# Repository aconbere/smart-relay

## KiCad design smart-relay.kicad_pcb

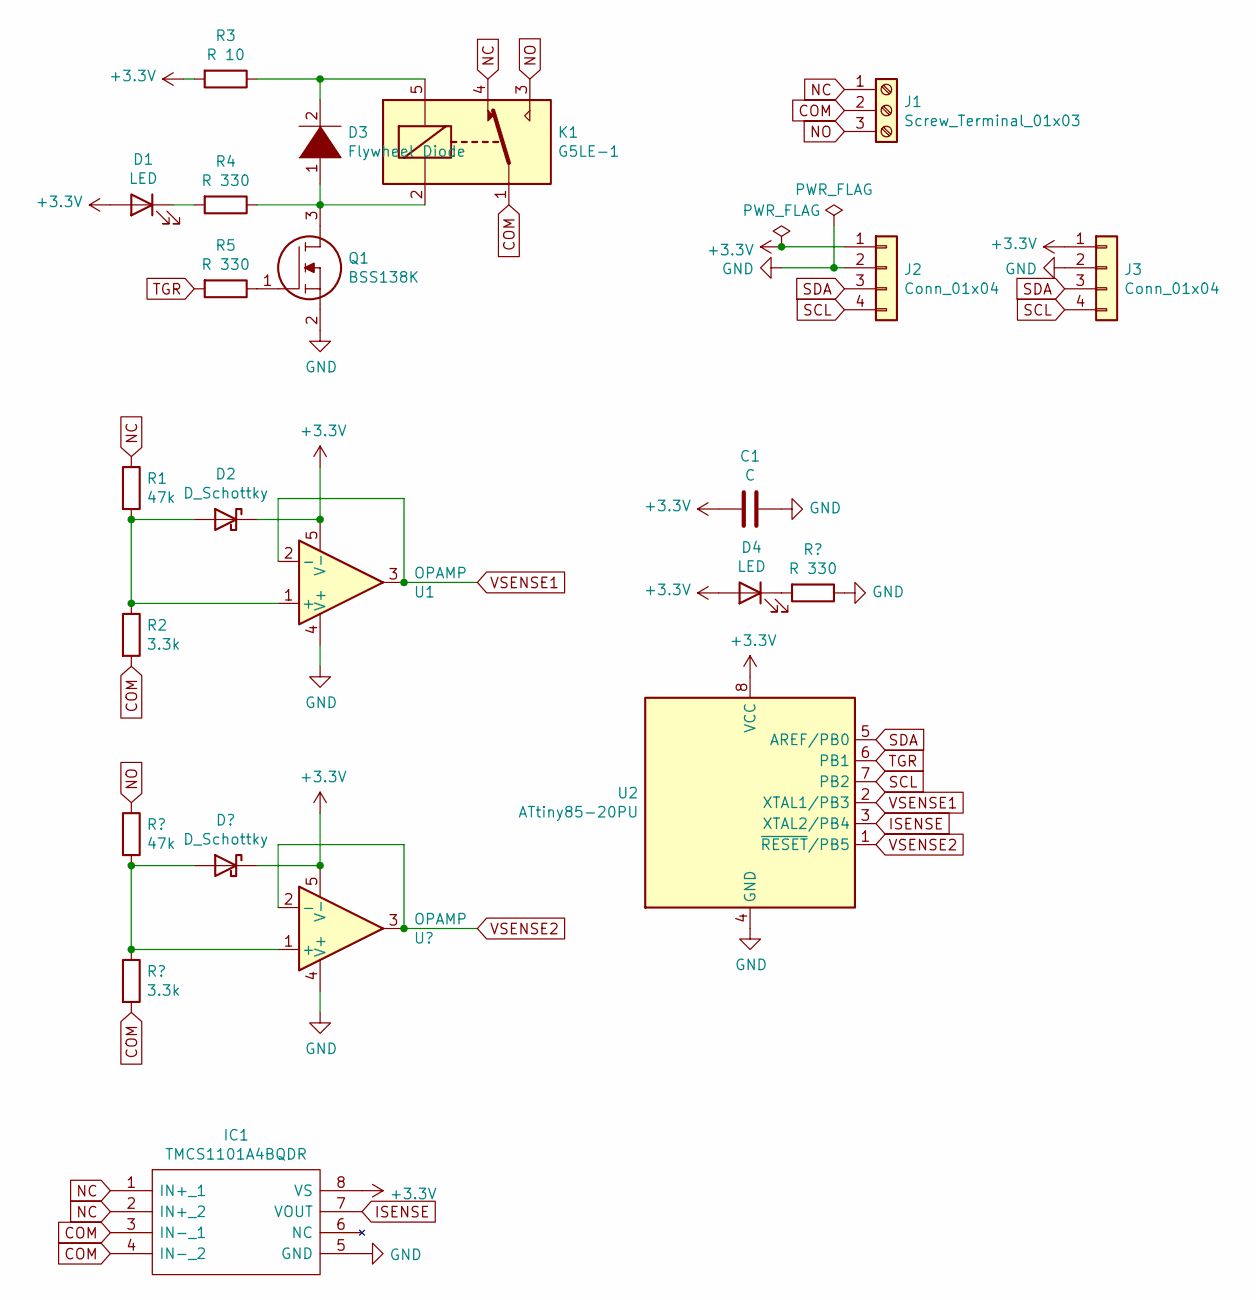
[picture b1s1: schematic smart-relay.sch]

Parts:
C1: C; K104K15X7RF53H5
D1, D4: LED; LTL4232
D2: D_Schottky; DIO_1N4447
D3: Flywheel Diode; DIOAD1410W60L470D235
IC1: TMCS1101A4BQDR; SOIC127P600X175-8N; Manufacturer_Part_Number TMCS1101A4BQDR; Mouser Part Number 595-TMCS1101A4BQDR
J1: Screw_Terminal_01x03; SHDR3W100P0X500_1X3_1500X900X1290P
J2: Conn_01x04; CONN_BM04B-SRSS-TB(LF)(SN)
J3: Conn_01x04; PinHeader_1x04_P2.54mm_Vertical
K1: G5LE-1; Relay_SPDT_Omron-G5LE-1
Q1: BSS138K; SOT96P237X111-3N; Manufacturer_Part_Number BSS138K; Mouser Part Number 512-BSS138K
R1: 47k; R_Axial_DIN0204_L3.6mm_D1.6mm_P1.90mm_Vertical
R2: 3.3k; R_Axial_DIN0204_L3.6mm_D1.6mm_P1.90mm_Vertical
R3: R 10; R_Axial_DIN0204_L3.6mm_D1.6mm_P1.90mm_Vertical
R4, R5: R 330; R_Axial_DIN0204_L3.6mm_D1.6mm_P1.90mm_Vertical
U1: OPAMP; SOT95P280X145-5N
U2: ATtiny85-20PU; DIP-8_W7.62mm

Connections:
+3V3: C1.2, D1.2 (A), D2.1 (K), D4.2 (A), IC1.8 (VS), J2.1, J3.1, R3.2, U1.5 (V-), U2.8 (VCC)
COM: IC1.3 (IN-_1), IC1.4 (IN-_2), J1.2, K1.1, R2.2
GND: C1.1, D4.1 (K), IC1.5 (GND), J2.2, J3.2, Q1.2, U1.4 (V+), U2.4 (GND)
ISENSE: IC1.7 (VOUT), U2.3 (XTAL2/PB4)
NC: IC1.1 (IN+_1), IC1.2 (IN+_2), J1.1, K1.4, R1.1
NO: J1.3, K1.3
unnamed: D1.1 (K), R4.2
unnamed: D2.2 (A), R1.2, R2.1, U1.1 (+)
unnamed: D3.1 (K), K1.2, Q1.3, R4.1
unnamed: D3.2 (A), K1.5, R3.1
unnamed: Q1.1, R5.1
SCL: J2.4, J3.4, U2.7 (PB2)
SDA: J2.3, J3.3, U2.5 (AREF/PB0)
TGR: R5.2, U2.6 (PB1)
VSENSE: U1.2 (-), U1.3, U2.2 (XTAL1/PB3)

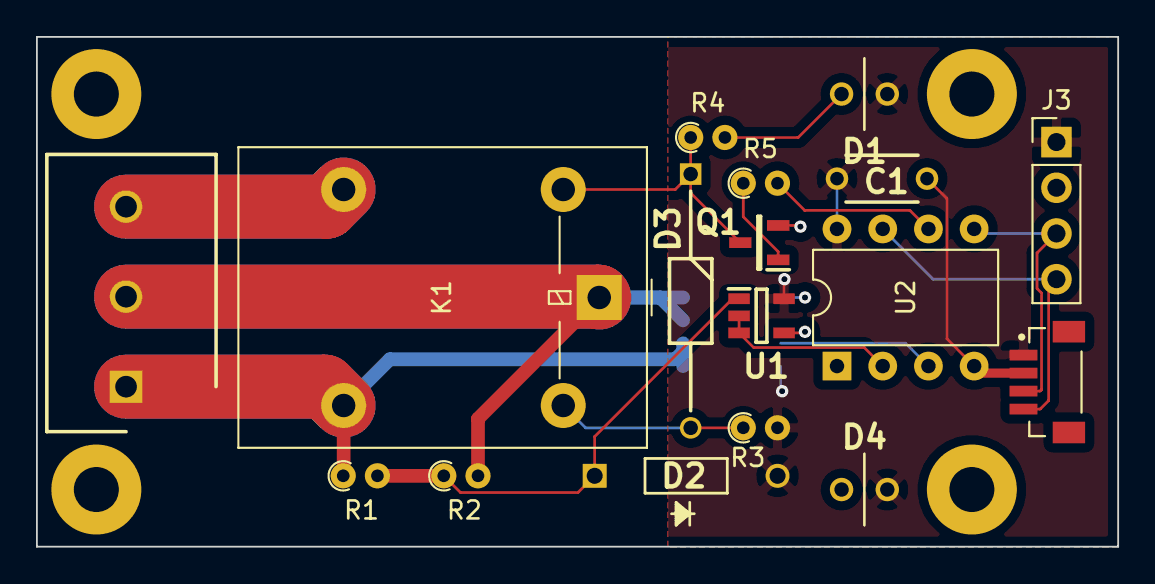
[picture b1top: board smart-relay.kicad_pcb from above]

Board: 2 copper layers, 60.1 x 28.3 mm, 18 parts (1 on the bottom side), 15 nets.

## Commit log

2020-11-25 make sure it saved
2020-11-25 separate hv line
2020-11-25 increase trace width for divider
2020-11-26 add thicker traces
2020-11-28 don't remember
2020-11-30 add decoupling cap and headers
2021-01-12 add another voltage sensor
